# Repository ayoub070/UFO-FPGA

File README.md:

# UFO-FPGA

The UFO-FPGA project is a collaborative effort by students and hobbyists, aimed at promoting and enhancing the excitement of working with Field-Programmable Gate Arrays (FPGAs). 

Our main objective is to develop an FPGA development board that follows the Arduino Uno format, making it easily accessible and familiar to users. The intention behind this project is to foster an open source community where users can contribute and build upon the existing files.

Key Features:
- The board supports communication with the FPGA through UART.
- The FPGA used in this project is the lattice ICE40HX4K, known for its versatility, performance and low power consumption .

Programming Options:
- Users have the flexibility to choose between different programming environments. They can utilize the closed-source ICecube 2 or leverage open source resources like apio (not yet working).

We welcome contributions from anyone interested in joining our mission to inspire students and hobbyists in the world of FPGAs. Feel free to explore the project, experiment with the board, and contribute to its ongoing development.

Please refer to the documentation and resources provided in this repository for detailed instructions on how to get started with the UFO-FPGA project.

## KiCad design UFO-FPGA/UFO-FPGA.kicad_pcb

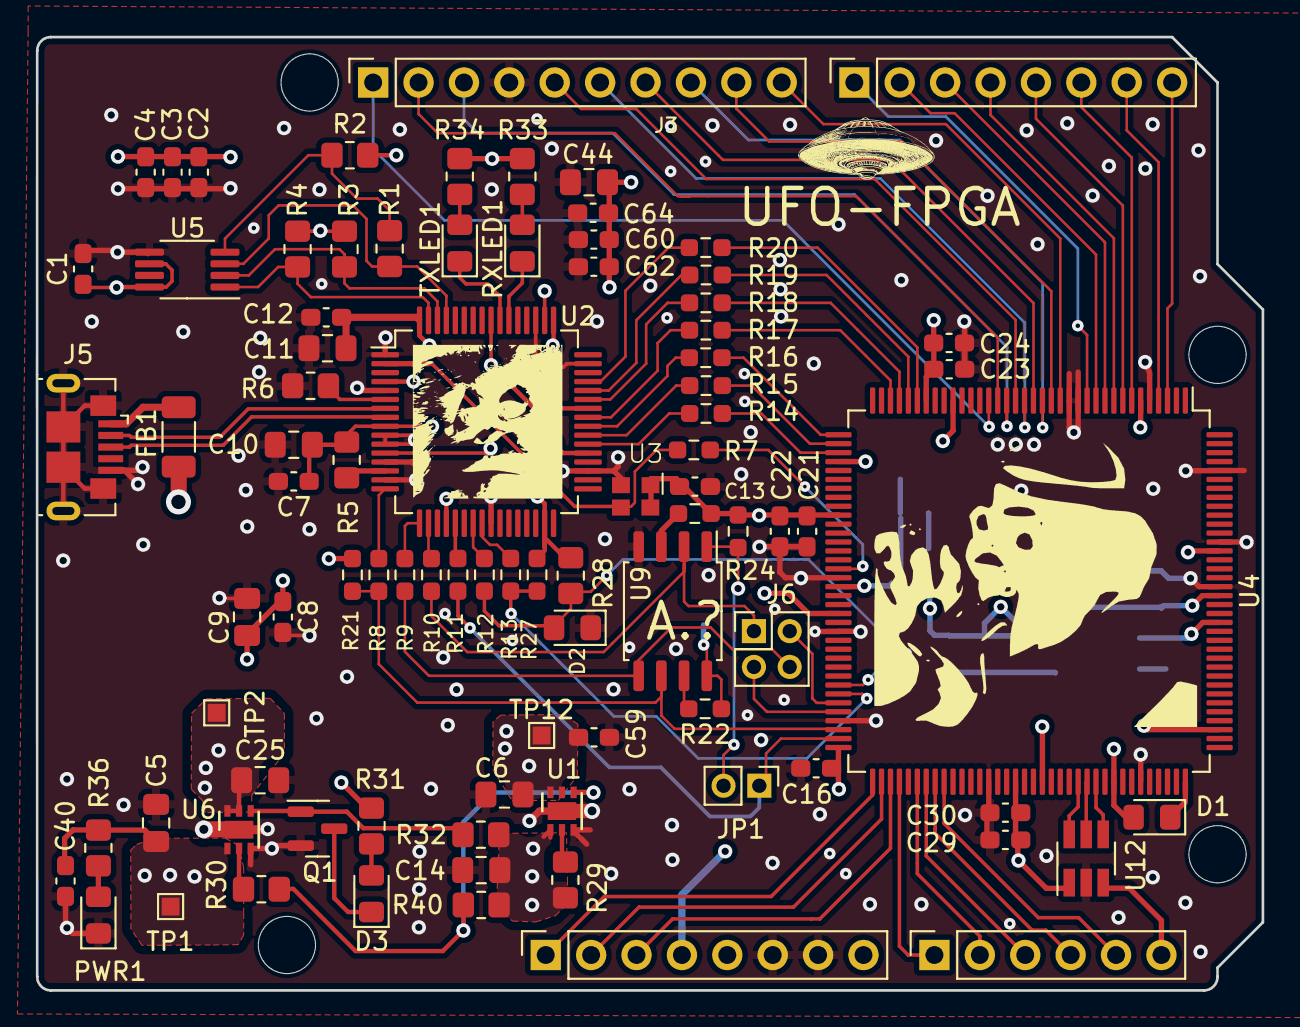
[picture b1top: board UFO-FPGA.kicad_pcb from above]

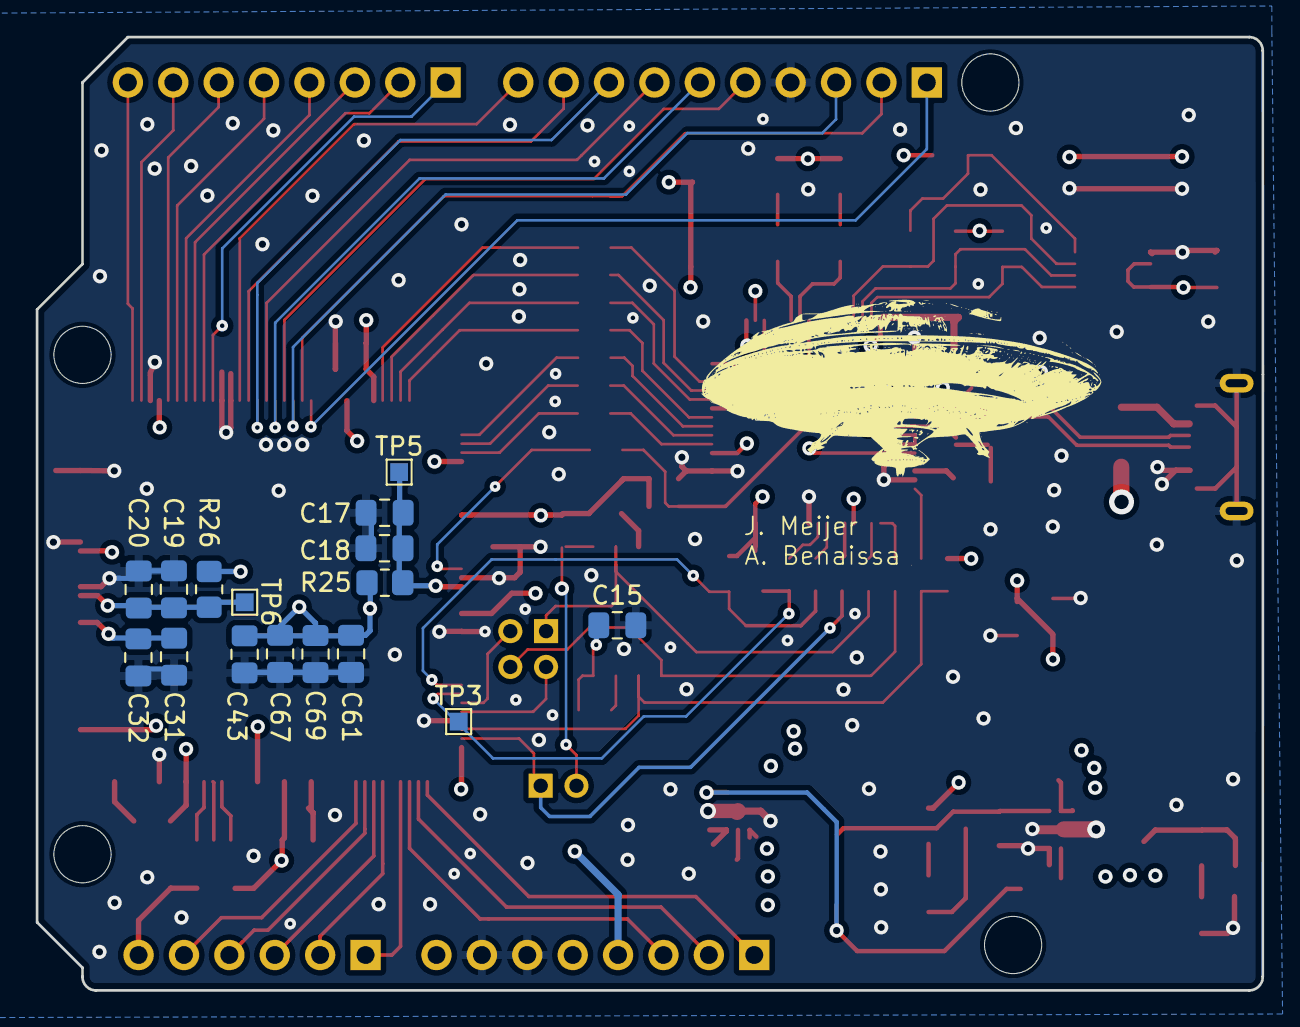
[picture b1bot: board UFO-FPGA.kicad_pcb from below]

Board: 4 copper layers, 68.6 x 53.3 mm, 108 parts (16 on the bottom side), 90 nets.

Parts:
C1, C7, C8, C12, C13, C16, C40, C62: 100nF; C_0603_1608Metric_Pad1.08x0.95mm_HandSolder
C2, C3, C4, C21, C22, C23, C24, C29, C30: 200nF; C_0603_1608Metric_Pad1.08x0.95mm_HandSolder
C5, C14: 1uF; C_0805_2012Metric_Pad1.18x1.45mm_HandSolder
C6, C11, C18, C19, C25, C43, C44: 10uF; C_0805_2012Metric_Pad1.18x1.45mm_HandSolder
C9, C10: 4u7F; C_0805_2012Metric_Pad1.18x1.45mm_HandSolder
C15, C17, C20: 100nF; C_0805_2012Metric_Pad1.18x1.45mm_HandSolder
C31, C32, C61, C67: 200nF; C_0805_2012Metric_Pad1.18x1.45mm_HandSolder
C59, C60: 1uF; C_0603_1608Metric_Pad1.08x0.95mm_HandSolder
C64: 10nF; C_0603_1608Metric_Pad1.08x0.95mm_HandSolder
C69: 10nF; C_0805_2012Metric_Pad1.18x1.45mm_HandSolder
D1: CDSU4148; D_0805_2012Metric_Pad1.15x1.40mm_HandSolder
D2: GREEN; LED_0805_2012Metric_Pad1.15x1.40mm_HandSolder
D3: POWER; LED_0805_2012Metric_Pad1.15x1.40mm_HandSolder
FB1: 600 Ohm, 500mA; L_1206_3216Metric_Pad1.22x1.90mm_HandSolder
J1: Power; PinSocket_1x08_P2.54mm_Vertical
J2: Digital; PinSocket_1x06_P2.54mm_Vertical
J3: Digital/PWM; PinSocket_1x10_P2.54mm_Vertical
J4: Digital; PinSocket_1x08_P2.54mm_Vertical
J5: USB_B_Micro; USB_Micro-B_GCT_USB3076-30-A
J6: Conn_02x02_Counter_Clockwise; PinHeader_2x02_P2.00mm_Vertical
JP1: Jumper_2_Open; PinHeader_1x02_P2.00mm_Vertical
MH1, MH2, MH3, MH4: MountingHole_3.2mm
PWR1: POWER; LED_0805_2012Metric_Pad1.15x1.40mm_HandSolder
Q1: 2N7002; SOT-23
R1, R5: 2K2; R_0805_2012Metric_Pad1.20x1.40mm_HandSolder
R2, R3, R4: 10K; R_0805_2012Metric_Pad1.20x1.40mm_HandSolder
R6: 12K; R_0805_2012Metric_Pad1.20x1.40mm_HandSolder
R7, R8, R9, R10, R11, R12, R13, R14, R15, R16, R17, R18, R19, R20: 0; R_0603_1608Metric_Pad0.98x0.95mm_HandSolder
R21, R22, R23, R24, R27: 10K; R_0603_1608Metric_Pad0.98x0.95mm_HandSolder
R25, R26: 100; R_0805_2012Metric_Pad1.20x1.40mm_HandSolder
R28: 690R; R_0805_2012Metric_Pad1.20x1.40mm_HandSolder
R29: 0R; R_0805_2012Metric_Pad1.20x1.40mm_HandSolder
R30: 0; R_0805_2012Metric_Pad1.20x1.40mm_HandSolder
R31: 330R; R_0805_2012Metric_Pad1.20x1.40mm_HandSolder
R32, R40: 10k; R_0805_2012Metric_Pad1.20x1.40mm_HandSolder
R33, R34: 220R; R_0805_2012Metric_Pad1.20x1.40mm_HandSolder
R36: 1K; R_0805_2012Metric_Pad1.20x1.40mm_HandSolder
RXLED1: RXLED; LED_0805_2012Metric_Pad1.15x1.40mm_HandSolder
TP1, TP2, TP3, TP5, TP6, TP12: TestPoint; TestPoint_Pad_1.0x1.0mm
TXLED1: TXLED; LED_0805_2012Metric_Pad1.15x1.40mm_HandSolder
U1: NCP187AMT120TAG (+1V2); DFN-6-1EP_2x2mm_P0.65mm_EP1x1.6mm
U2: FT2232HL; LQFP-64_10x10mm_P0.5mm
U3: ASDMB-12MHz; ASDDV-12.000MHz-LC-T3
U4: ICE40HX4K-TQ144; TQFP-144_20x20mm_P0.5mm
U5: 93LC56CT-I/MS; MSOP-8_3x3mm_P0.65mm
U6: NCP187AMT330TAG (+3V3); DFN-6-1EP_2x2mm_P0.65mm_EP1x1.6mm
U9: N25Q032A13ESC40F; SSOP-8_5.25x5.24mm_P1.27mm
U12: MAX11116AUT+T; SOT-23-6_Handsoldering

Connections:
+1V2: C6.1, C43.1, C59.1, C61.1, C67.1, C69.1, R25.2, R26.1, TP12.1, U1.5 (SNS), U1.6 (OUT), U4.27 (VCC), U4.40 (VCC), U4.92 (VCC), U4.111 (VCC)
+1V8: C11.1, C12.1, U2.12 (VCORE), U2.37 (VCORE), U2.49 (VREGOUT), U2.64 (VCORE)
+2V5: D1.1 (K), U4.108 (VPP_2V5)
+3V3: C1.1, C2.1, C3.1, C4.1, C7.1, C8.1, C9.1, C10.1, C13.1, C15.1, C16.1, C21.1, C22.1, C23.1, C24.1, C25.1, C29.1, C30.1, C31.1, C32.1, C44.1, C60.1, C62.1, C64.1, D1.2 (A), J1.4, R2.2, R3.2, R4.2, R5.2, R21.1, R22.1, R23.1, R24.1, R27.1, R28.1, R31.1, R33.2, R34.2, TP2.1, U2.4 (VPHY), U2.9 (VPLL), U2.20 (VCCIO), U2.31 (VCCIO), U2.42 (VCCIO), U2.50 (VREGIN), U2.56 (VCCIO), U3.1 (Standby), U3.4 (VDD), U4.6 (VCCIO_3), U4.30 (VCCIO_3), U4.46 (VCCIO_2), U4.57 (VCCIO_2), U4.72 (VCC_SPI), U4.89 (VCCIO_1), U4.100 (VCCIO_1), U4.123 (VCCIO_0), U4.131 (VCCIO_0), U5.6 (ORG), U5.8 (Vcc), U6.5 (SNS), U6.6 (OUT), U9.8 (Vcc), U12.1 (VDD)
+5V: C5.1, C14.1, C40.1, FB1.1, J1.5, R29.2, R32.2, R36.1, R40.2, TP1.1, U1.1 (IN), U6.1 (IN)
/BANK 4 - SPI Programming/ICE_MISO: J6.2, U4.67 (IOB_105_SDO)
/BANK 4 - SPI Programming/ICE_MOSI: J6.3, U4.68 (IOB_106_SDI)
/BANK 4 - SPI Programming/N25-CS: JP1.2 (B), R24.2, U9.1 (CS)
/BANK 4 - SPI Programming/N25-HOLD: R22.2, U9.7 (HOLD)
/BANK 4 - SPI Programming/N25-WP: R23.2, U9.3 (Wp)
/BANK 4 - SPI Programming/VCCPLL0: C17.1, C18.1, R25.1, TP5.1, U4.54 (VCCPLL0)
/BANK 4 - SPI Programming/VCCPLL1: C19.1, C20.1, R26.2, TP6.1, U4.126 (VCCPLL1)
/POWER/3v3-EN: R30.1, U6.2 (EN)
/POWER/LED-ON: D3.1 (K), Q1.3 (D)
/POWER/PG1V2: R30.2, R40.1, U1.4 (PG)
/POWER/PG3v3: Q1.1 (G), R32.1, U6.4 (PG)
/POWER/RIND-ON: D3.2 (A), R31.2
/USB Programmer/CTSn-ft: R17.1, U2.41 (BDBUS3)
/USB Programmer/DCDn-ft: R20.1, U2.45 (BDBUS6)
/USB Programmer/DSRn-ft: R19.1, U2.44 (BDBUS5)
/USB Programmer/DTRn-ft: R18.2, U2.43 (BDBUS4)
/USB Programmer/EE-CLK: R3.1, U2.62 (EECLK), U5.2 (CLK)
/USB Programmer/EE-CS: R4.1, U2.63 (EECS), U5.1 (CS)
/USB Programmer/EE-D: R1.2, U2.61 (EEDATA), U5.3 (DI)
/USB Programmer/EE-DO: R1.1, R2.1, U5.4 (DO)
/USB Programmer/FLASH_MISO: R10.2, U2.18 (ADBUS2)
/USB Programmer/FLASH_MOSI: R9.2, U2.17 (ADBUS1)
/USB Programmer/FTD-OSCI: R7.1, U2.2 (OSCI), U3.3 (Out)
/USB Programmer/ICE-CDONE: R12.2, U2.23 (ADBUS6)
/USB Programmer/ICE-CREST: R13.2, U2.24 (ADBUS7)
/USB Programmer/ICE-SCK: R8.2, U2.16 (ADBUS0)
/USB Programmer/ICE-SS-B: R11.2, U2.21 (ADBUS4)
/USB Programmer/RS232-Rx-TTL: R14.2, U2.38 (BDBUS0)
/USB Programmer/RS232-Tx-TTL: R15.2, U2.39 (BDBUS1)
/USB Programmer/RTSn-ft: R16.1, U2.40 (BDBUS2)
/USB Programmer/ftd-ref: R6.1, U2.6 (REF)
/USB Programmer/ftd-reset: R5.1, U2.14 (~RESET)
/USB Programmer/rxled out: RXLED1.1 (K), U2.54 (BCBUS3)
/USB Programmer/rxled-mid: R33.1, RXLED1.2 (A)
/USB Programmer/txled out: TXLED1.1 (K), U2.55 (BCBUS4)
/USB Programmer/txled-mid: R34.1, TXLED1.2 (A)
ADC-CS: U4.98 (IOR_148), U12.4 (CS)
AIN1: J2.6, U12.3 (AIN)
CTSn: R17.2, U4.34 (IOL_25B)
D+: J5.3 (D+), U2.8 (DP)
D-: J5.2 (D-), U2.7 (DM)
DCDn: R20.2, U4.31 (IOL_24A)
DSRn: R19.2, U4.32 (IOL_24B)
DTRn: R18.1, U4.33 (IOL_25A)
Flash-MISO: J6.1, R10.1, U9.2 (SDO)
Flash-MOSI: J6.4, R9.1, U9.5 (SDI)
GND: C1.2, C2.2, C3.2, C4.2, C5.2, C6.2, C7.2, C8.2, C9.2, C10.2, C11.2, C12.2, C13.2, C14.2, C15.2, C16.2, C17.2, C18.2, C19.2, C20.2, C21.2, C22.2, C23.2, C24.2, C25.2, C29.2, C30.2, C31.2, C32.2, C40.2, C43.2, C44.2, C59.2, C60.2, C61.2, C62.2, C64.2, C67.2, C69.2, D2.1 (K), J1.6, J1.7, J3.4, J5.5 (GND), J5.6 (Shield), PWR1.1 (K), Q1.2 (S), R6.2, U1.3 (GND), U1.7 (GND), U2.1 (GND), U2.5 (GND), U2.10 (AGND), U2.11 (GND), U2.13 (TEST), U2.15 (GND), U2.25 (GND), U2.35 (GND), U2.47 (GND), U2.51 (GND), U3.2 (GND), U4.5 (GND), U4.13 (GND), U4.14 (GND), U4.53 (GNDPLL0), U4.59 (GND), U4.69 (GND), U4.86 (GND), U4.103 (GND), U4.127 (GNDPLL1), U4.132 (GND), U4.140 (GND), U5.5 (Vss), U6.3 (GND), U6.7 (GND), U9.4 (Vss), U12.2 (GND)
ICE_CDONE: D2.2 (A), R12.1, R28.2, U4.65 (CDONE)
ICE_CLK: R7.2, U4.52 (IOB_82_GBIN4)
ICE_CREST: R13.1, R27.2, TP3.1, U4.66 (~CRESET)
ICE_SCK: R8.1, R21.2, U4.70 (IOB_107_SCK), U9.6 (SCK)
ICE_SS_B: JP1.1 (A), R11.1, U4.71 (IOB_108_SS)
MISO: U4.97 (IOR_147), U12.5 (DOUT)
unnamed: PWR1.2 (A), R36.2
unnamed: R29.1, U1.2 (EN)
PIN-1: J3.1, U4.23 (IOL_17A)
PIN-2: J3.2, U4.22 (IOL_14B)
PIN-3: J3.3, U4.21 (IOL_14A_GBIN6)
PIN-4: J3.5, U4.20 (IOL_13B_GBIN7)
PIN-5: J3.6, U4.19 (IOL_13A)
PIN-6: J3.7, U4.18 (IOL_12B)
PIN-7: J3.8, U4.17 (IOL_12A)
PIN-8: J3.9, U4.16 (IOL_10B)
PIN-9: J3.10, U4.15 (IOL_10A)
PIN-10: J4.1, U4.12 (IOL_8B)
PIN-11: J4.2, U4.11 (IOL_8A)
PIN-12: J4.3, U4.10 (IOL_5B)
PIN-13: J4.4, U4.9 (IOL_5A)
PIN-14: J4.5, U4.8 (IOL_4B)
PIN-15: J4.6, U4.7 (IOL_4A)
PIN-16: J4.7, U4.4 (IOL_3B)
PIN-17: J4.8, U4.3 (IOL_3A)
PIN-18: J2.5, U4.81 (IOR_117)
PIN-19: J2.4, U4.80 (IOR_116)
PIN-20: J2.3, U4.79 (IOR_115)
PIN-21: J2.2, U4.78 (IOR_114)
PIN-22: J2.1, U4.76 (IOR_112)
PIN-23: J1.3, U4.75 (IOR_111)
PIN-24: J1.2, U4.74 (IOR_110)
PIN-25: J1.1, U4.73 (IOR_109)
RS232_Rx_TTL: R14.1, U4.39 (IOB_61)
RS232_Tx_TTL: R15.1, U4.38 (IOB_57)
RTSn: R16.2, U4.37 (IOB_56)
SCK: U4.96 (IOR_146), U12.6 (SCLK)
Vin: FB1.2, J5.1 (VBUS)

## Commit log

2023-03-11 monkey
2023-03-11 Update Read.me.txt
    Big monkey
2023-04-21 Add files via upload
    Updated to v0.2
2023-04-21 Moved items
2023-04-21 Explainer
2023-04-21 pinout tab
2023-04-22 Power schematisch gemaakt
2023-04-22 Added net labels
2023-04-22 symbols
2023-04-22 Pinout for ADC
2023-04-22 WLP-8 added
2023-04-23 ADC schematic met note's
2023-04-23 Labels and schametic changes
    Updated Power schematic
    Added labes for the different nets
2023-04-23 spatie weg gehaald
2023-04-24 Test van ground enable gedaan en foto toegevoeg
    De enable werkt
2023-04-25 Arduino PCB
    Added Arduino PCB format
2023-04-25 nano Delete
2023-04-25 Fixed text and placement
2023-04-25 Dual ramp MC34 inverting converter added
2023-04-25 pins and USB
2023-04-25 De inverting supply schakeling gemaakt
2023-04-25 IO and power
2023-04-25 Opamp gemaakt van de ADC
    Enkel nog begrijpen wat VDC is. Aan docent vragen?
2023-04-25 Revision
2023-04-25 PCB and footprint
    Added foorprints and moved on pcb layout
2023-04-26 edge cuts
2023-04-26 footprints and PCB
2023-04-26 Nieuwe ADC conmponent
2023-04-26 Schakeling ADC gemaakt 1 opamp weg gehaald
2023-04-26 footprint
2023-04-26 Weerstanden waardes verandert en namen verandert
2023-04-26 Footprints and values
2023-04-26 Weerstand veranderd Waardoor er minder stroom loopt naar de opamp want er is niet veel stroom nodig
2023-04-27 PCB planes
    Added:
    added Power plane +1v2, +3v3 and +5v on layer 4
    Ground plane on layer 2 and 5
    Added signal layer 1,3 and 6
2023-04-27 Vregout
2023-04-27 ubs shield
2023-04-28 PCB
    many pcb changes
    -started routing
    -added vias
    -power planes
    -ground planes
2023-04-28 pcb update
2023-04-28 DRC run
2023-04-29 pcb prog redesign
2023-04-30 pcb placement
2023-04-30 PCB placement
    spi connected
2023-05-01 pcb 0603
2023-05-01 pcb and footprints
    0603
2023-05-01 0603
2023-05-01 pcb
    added John zendong
2023-05-05 pcb
    added monkey
2023-05-06 vias and silkscreen
2023-05-07 Added UFO
2023-05-08 pcb silkscreen
2023-05-09 power
2023-05-11 plot
2023-05-11 monkey 2
2023-05-12 3v3 traces
2023-05-12 ufo board png
2023-05-12 Wat warnings weg gewerkt gerber file gemaakt met de drill files ze staan in gerber-test
2023-06-05 schema
2023-06-24 Readme geupdate
    Moet nog wel wat technische dingen bij komen maar dit is wel een mooie opzet
2023-06-24 Foutje uit readme gehaald
2023-07-01 changed gerber name
2023-07-01 Remove unnessesary
